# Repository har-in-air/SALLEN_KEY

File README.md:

# Stereo 2-way 2nd order active crossover (Sallen Key)

Crossover frequency Fc = 1/( 2 * pi * R * C)

In the schematic, R = 5.6K, C = 100nF, so Fc ~= 284 Hz.

## Top

## Bottom

## 2.1 option
For a 2.1 amplifier filter configuration:  

* Do not populate R12, R18, C14, C16, C19
* Populate R6
* Populate R10 so that the unused opamp U2B +input is not floating.
* Solder a jumper wire across x1, x2 points in the schematic
* The summed low-pass filter output is on LLo output

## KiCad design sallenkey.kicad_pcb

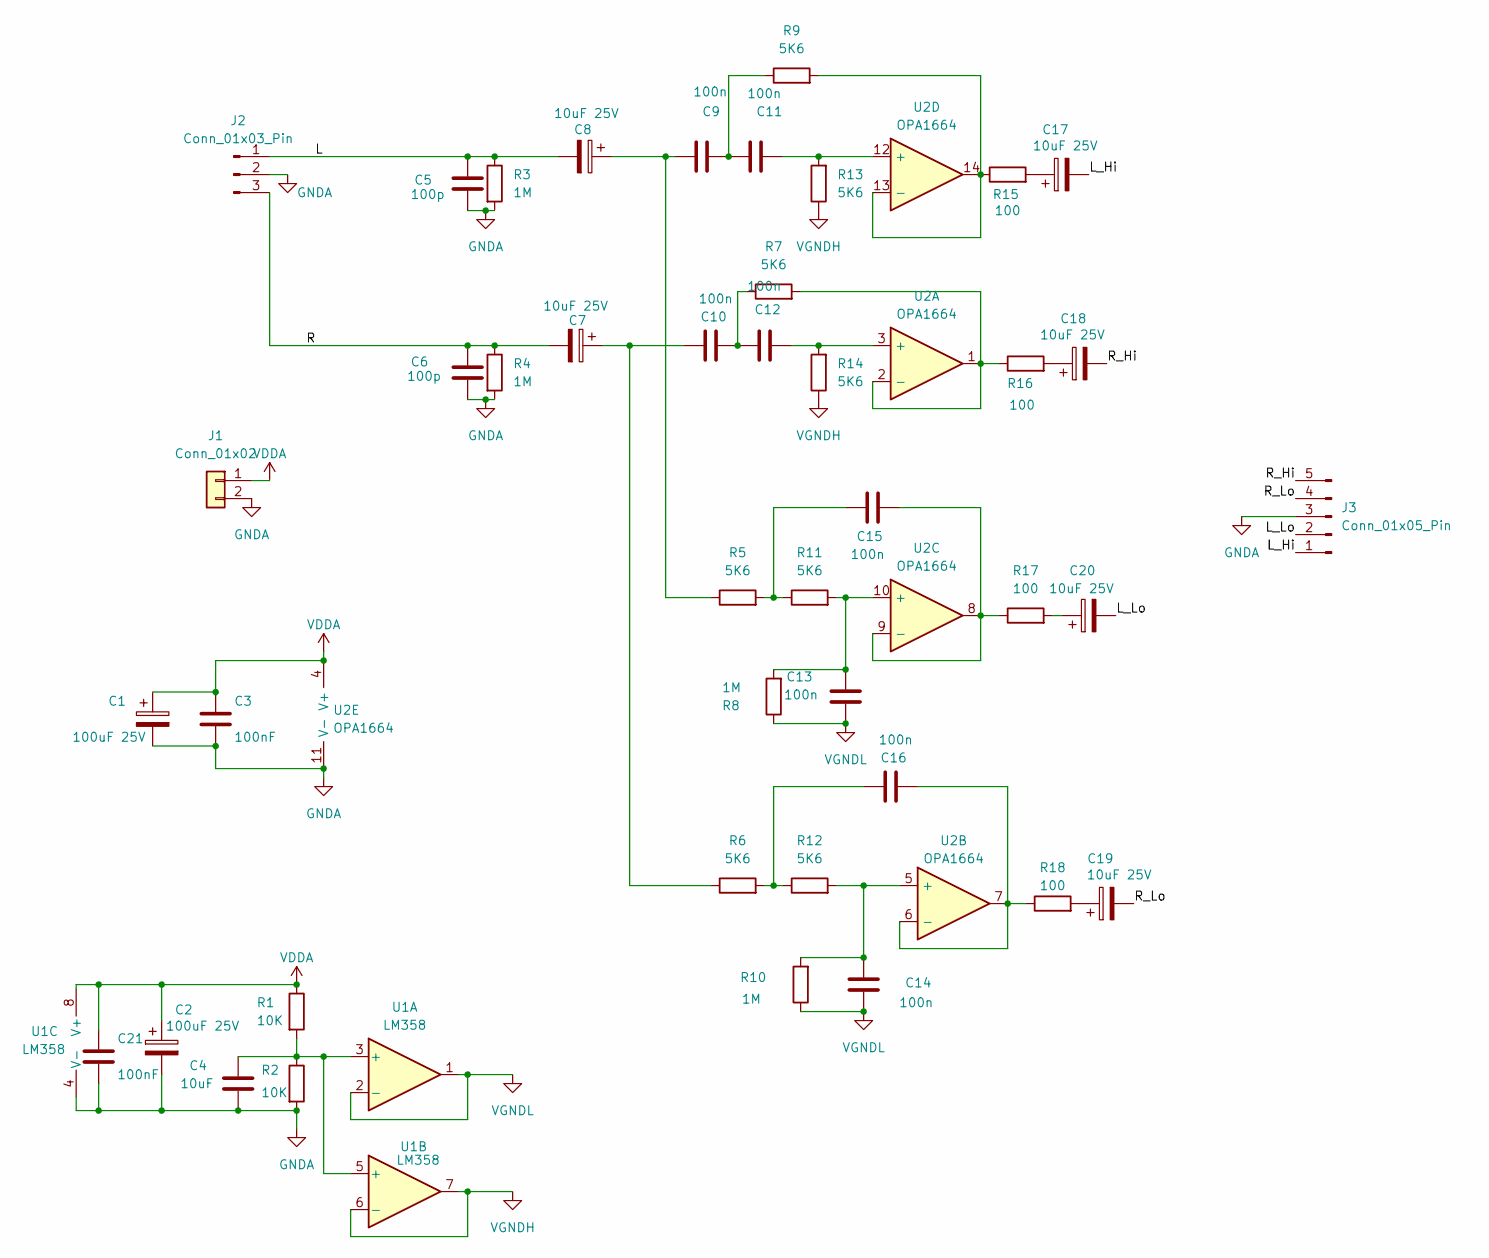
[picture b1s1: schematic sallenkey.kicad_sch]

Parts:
C1, C2: 100uF 25V; CP_Elec_6.3x7.7
C3, C21: 100nF; C_0805_2012Metric_Pad1.18x1.45mm_HandSolder
C4: 10uF; C_0805_2012Metric_Pad1.18x1.45mm_HandSolder
C5, C6: 100p; C_0805_2012Metric_Pad1.18x1.45mm_HandSolder
C7, C8, C17, C18, C19, C20: 10uF 25V; CP_Elec_6.3x7.7
C9, C10, C11, C12, C13, C14, C15, C16: 100n; C_Rect_L7.0mm_W2.0mm_P5.00mm
J1: Conn_01x02; PinHeader_1x02_P2.54mm_Vertical
J2: Conn_01x03_Pin; PinHeader_1x03_P2.54mm_Vertical
J3: Conn_01x05_Pin; PinHeader_1x05_P2.54mm_Vertical
R1, R2: 10K; R_0805_2012Metric_Pad1.20x1.40mm_HandSolder
R3, R4, R8, R10: 1M; R_0805_2012Metric_Pad1.20x1.40mm_HandSolder
R5, R6, R7, R9, R11, R12, R13, R14: 5K6; R_0805_2012Metric_Pad1.20x1.40mm_HandSolder
R15, R16, R17, R18: 100; R_1206_3216Metric_Pad1.30x1.75mm_HandSolder
U1: LM358; SOIC-8_3.9x4.9mm_P1.27mm
U2: OPA1664; SOIC-14_3.9x8.7mm_P1.27mm

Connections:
/L: C5.1, C8.2, J2.1, R3.1
/L_Hi: C17.2, J3.1
/L_Lo: C20.2, J3.2
/R: C6.1, C7.2, J2.3, R4.1
/R_Hi: C18.2, J3.5
/R_Lo: C19.2, J3.4
GNDA: C1.2, C2.2, C3.2, C4.2, C5.2, C6.2, C21.2, J1.2, J2.2, J3.3, R2.2, R3.2, R4.2, U1.4 (V-), U2.11 (V-)
unnamed: C8.1, C9.2, R5.1
unnamed: C10.1, C12.2, R7.1
unnamed: C7.1, C10.2, R6.1
unnamed: C9.1, C11.2, R9.1
unnamed: C15.1, R5.2, R11.1
unnamed: C16.2, R6.2, R12.1
unnamed: C17.1, R15.2
unnamed: C18.1, R16.2
unnamed: C19.1, R18.2
unnamed: C20.1, R17.2
unnamed: C4.1, R1.2, R2.1, U1.3 (+), U1.5 (+)
unnamed: C12.1, R14.2, U2.3 (+)
unnamed: R7.2, R16.1, U2.1, U2.2 (-)
unnamed: C14.2, R10.2, R12.2, U2.5 (+)
unnamed: C16.1, R18.1, U2.6 (-), U2.7
unnamed: C13.2, R8.2, R11.2, U2.10 (+)
unnamed: C15.2, R17.1, U2.8, U2.9 (-)
unnamed: C11.1, R13.2, U2.12 (+)
unnamed: R9.2, R15.1, U2.13 (-), U2.14
VDDA: C1.1, C2.1, C3.1, C21.1, J1.1, R1.1, U1.8 (V+), U2.4 (V+)
VGNDH: R13.1, R14.1, U1.6 (-), U1.7
VGNDL: C13.1, C14.1, R8.1, R10.1, U1.1, U1.2 (-)

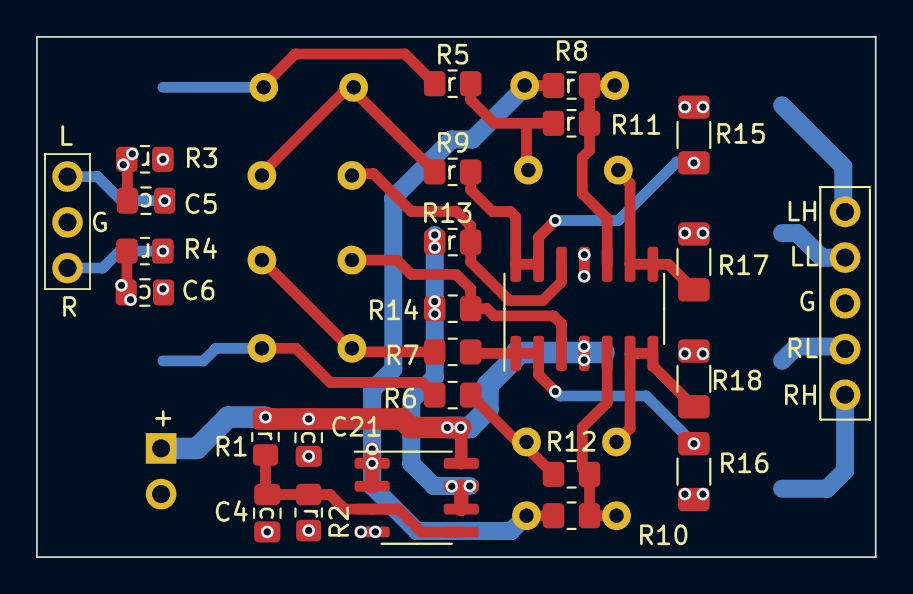
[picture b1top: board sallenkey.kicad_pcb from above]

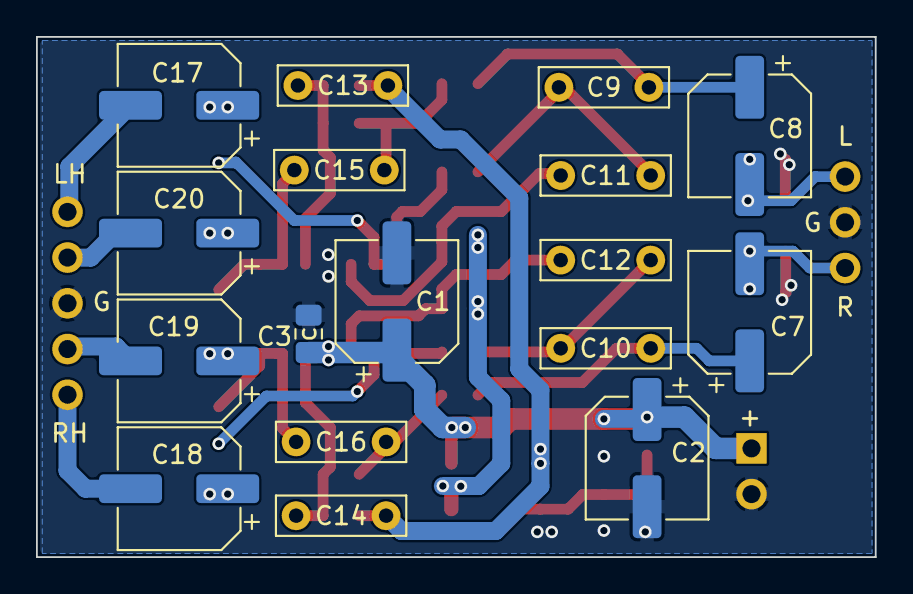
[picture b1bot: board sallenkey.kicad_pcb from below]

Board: 2 copper layers, 46.6 x 28.9 mm, 44 parts (17 on the bottom side), 29 nets.
